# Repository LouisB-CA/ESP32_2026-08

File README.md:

# A Project for ESP32 Scratchwork
**2026-08-10**

### Rough Timeline
* Aug 2026 -- write sketches for breadboard circuit
* Sep 2026 -- layout and assemble perfboard version
* Oct 2026 -- write sketches for the perfboard assembly

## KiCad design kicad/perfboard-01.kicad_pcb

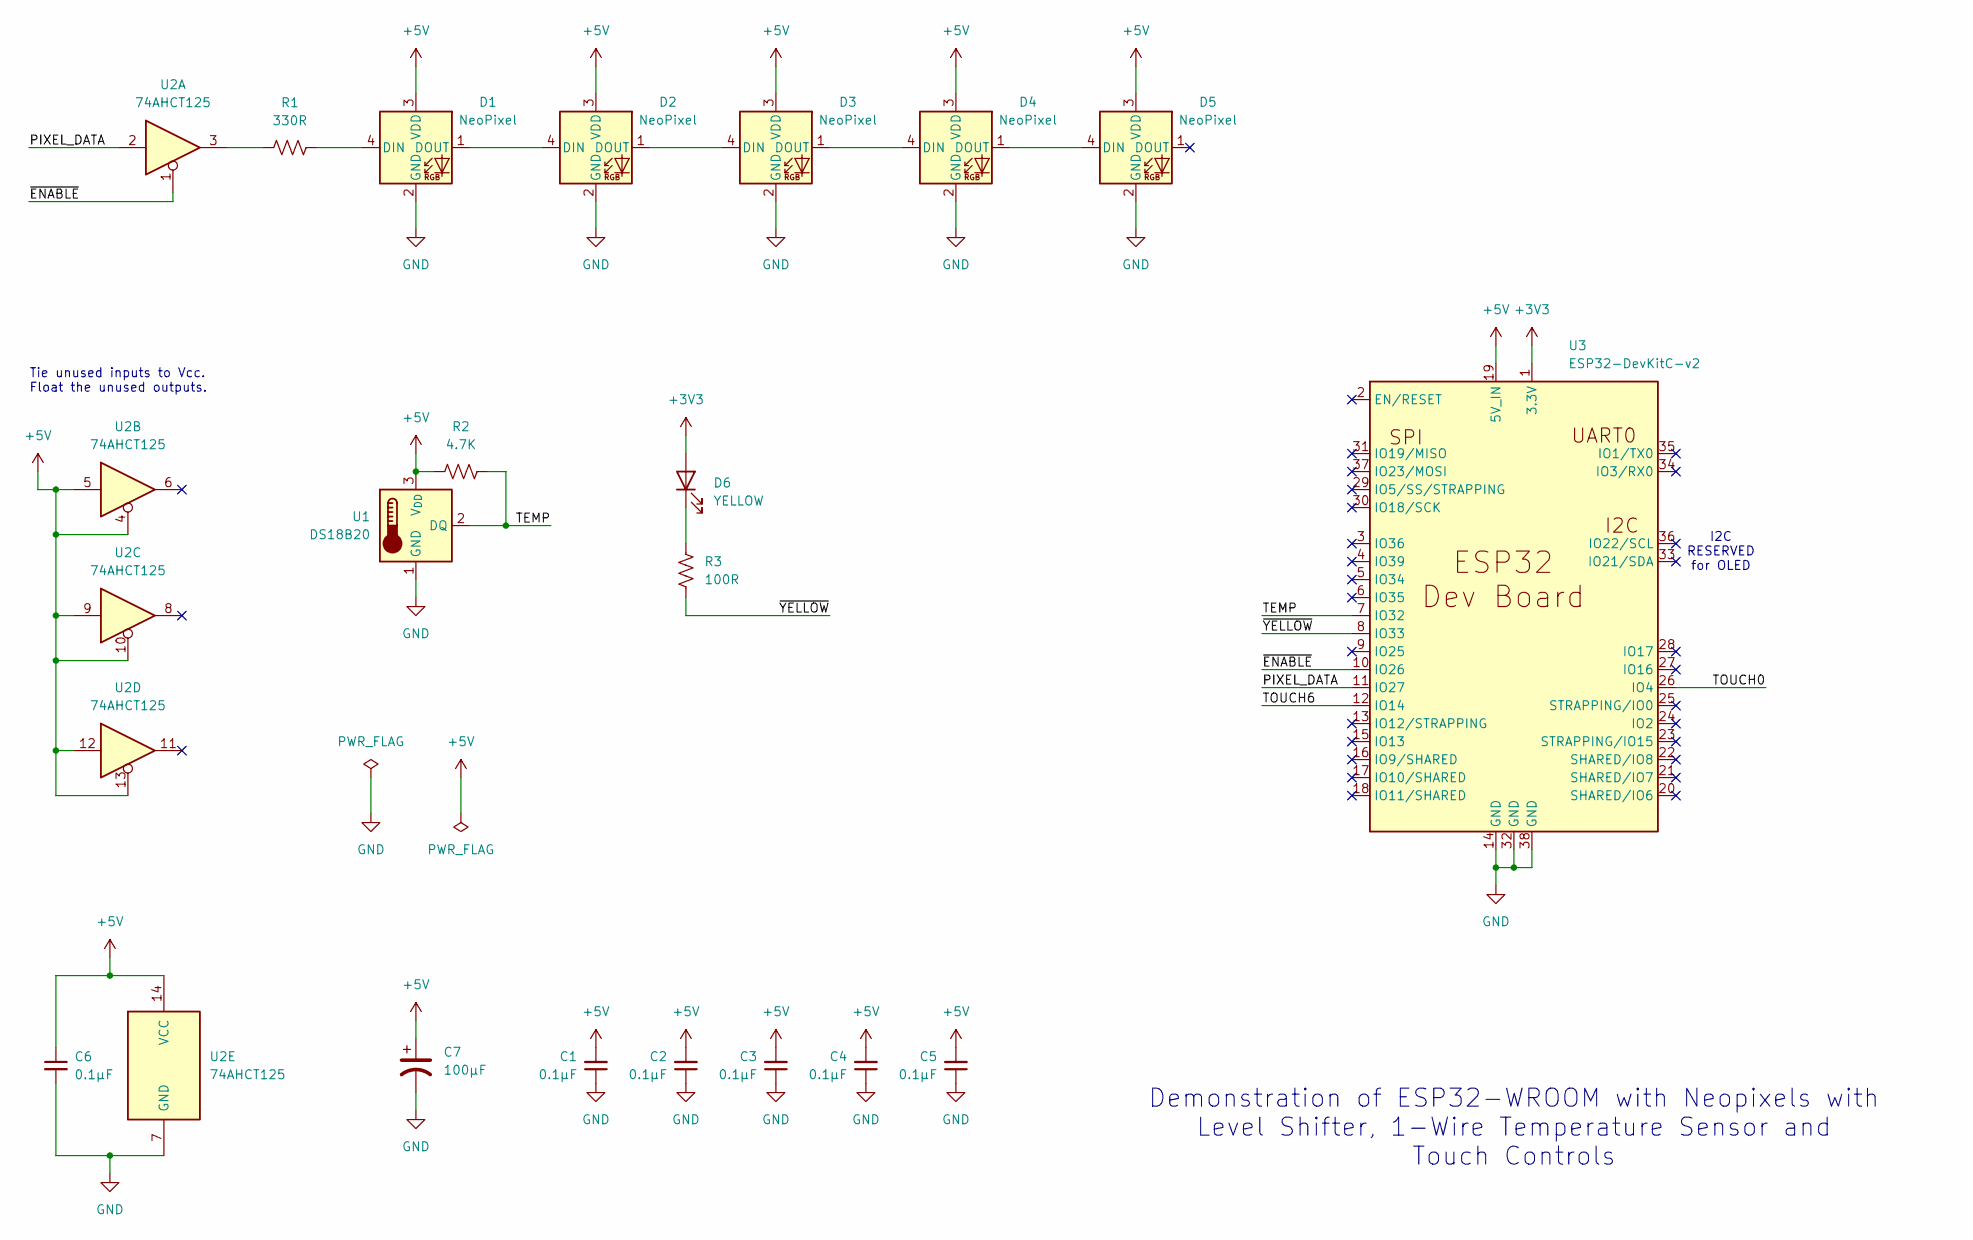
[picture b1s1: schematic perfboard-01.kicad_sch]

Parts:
C1, C2, C3, C4, C5, C6: 0.1µF; C_Disc_D3.4mm_W2.1mm_P2.50mm
C7: 100µF; C_Radial_D5.0mm_H11.0mm_P2.00mm
D1, D2, D3, D4, D5: NeoPixel; Neopixel_1x04_P2.54mm_Vertical_Mounted
D6: YELLOW; LED_D3.0mm_Horizontal_O6.35mm_Z6.0mm
R1: 330R; R_Axial_DIN0309_L9.0mm_D3.2mm_P12.70mm_Horizontal
R2: 4.7K; R_Axial_DIN0207_L6.3mm_D2.5mm_P10.16mm_Horizontal
R3: 100R; R_Axial_DIN0207_L6.3mm_D2.5mm_P10.16mm_Horizontal
U1: DS18B20; TO-92_Inline
U2: 74AHCT125; CERDIP-14_W7.62mm_SideBrazed
U3: ESP32-DevKitC-v2; ESP32-DevKitC_inverted

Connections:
+3V3: D6.2 (A), U3.1 (3.3V)
+5V: C1.2, C2.2, C3.2, C4.2, C5.2, C6.1, C7.1, D1.3 (VDD), D2.3 (VDD), D3.3 (VDD), D4.3 (VDD), D5.3 (VDD), R2.1, U1.3 (V_{DD}), U2.4, U2.5, U2.9, U2.10, U2.12, U2.13, U2.14 (VCC), U3.19 (5V_IN)
/PIXEL_DATA: U2.2, U3.11 (IO27)
/TEMP: R2.2, U1.2 (DQ), U3.7 (IO32)
/TOUCH0: U3.26 (IO4)
/TOUCH6: U3.12 (IO14)
/~ENABLE: U2.1, U3.10 (IO26)
/~YELLOW: R3.2, U3.8 (IO33)
GND: C1.1, C2.1, C3.1, C4.1, C5.1, C6.2, C7.2, D1.2 (GND), D2.2 (GND), D3.2 (GND), D4.2 (GND), D5.2 (GND), U1.1 (GND), U2.7 (GND), U3.14 (GND), U3.32 (GND), U3.38 (GND)
unnamed: D1.4 (DIN), R1.2
unnamed: D1.1 (DOUT), D2.4 (DIN)
unnamed: D2.1 (DOUT), D3.4 (DIN)
unnamed: D3.1 (DOUT), D4.4 (DIN)
unnamed: D4.1 (DOUT), D5.4 (DIN)
unnamed: D6.1 (K), R3.1
unnamed: R1.1, U2.3

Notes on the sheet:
I2C RESERVED for OLED
Demonstration of ESP32-WROOM with Neopixels with Level Shifter, 1-Wire Temperature Sensor and Touch Controls
Tie unused inputs to Vcc. Float the unused outputs.

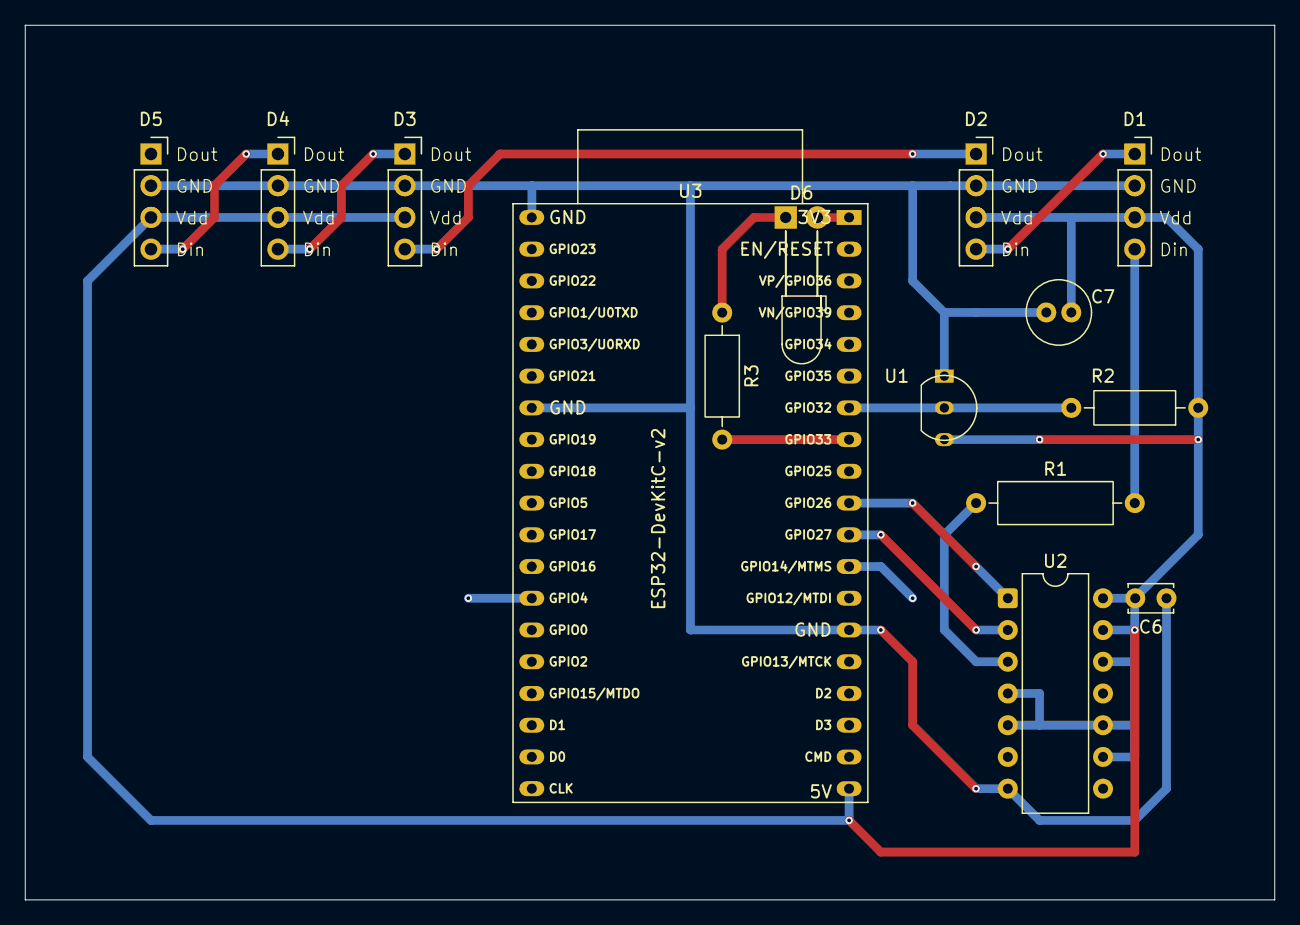
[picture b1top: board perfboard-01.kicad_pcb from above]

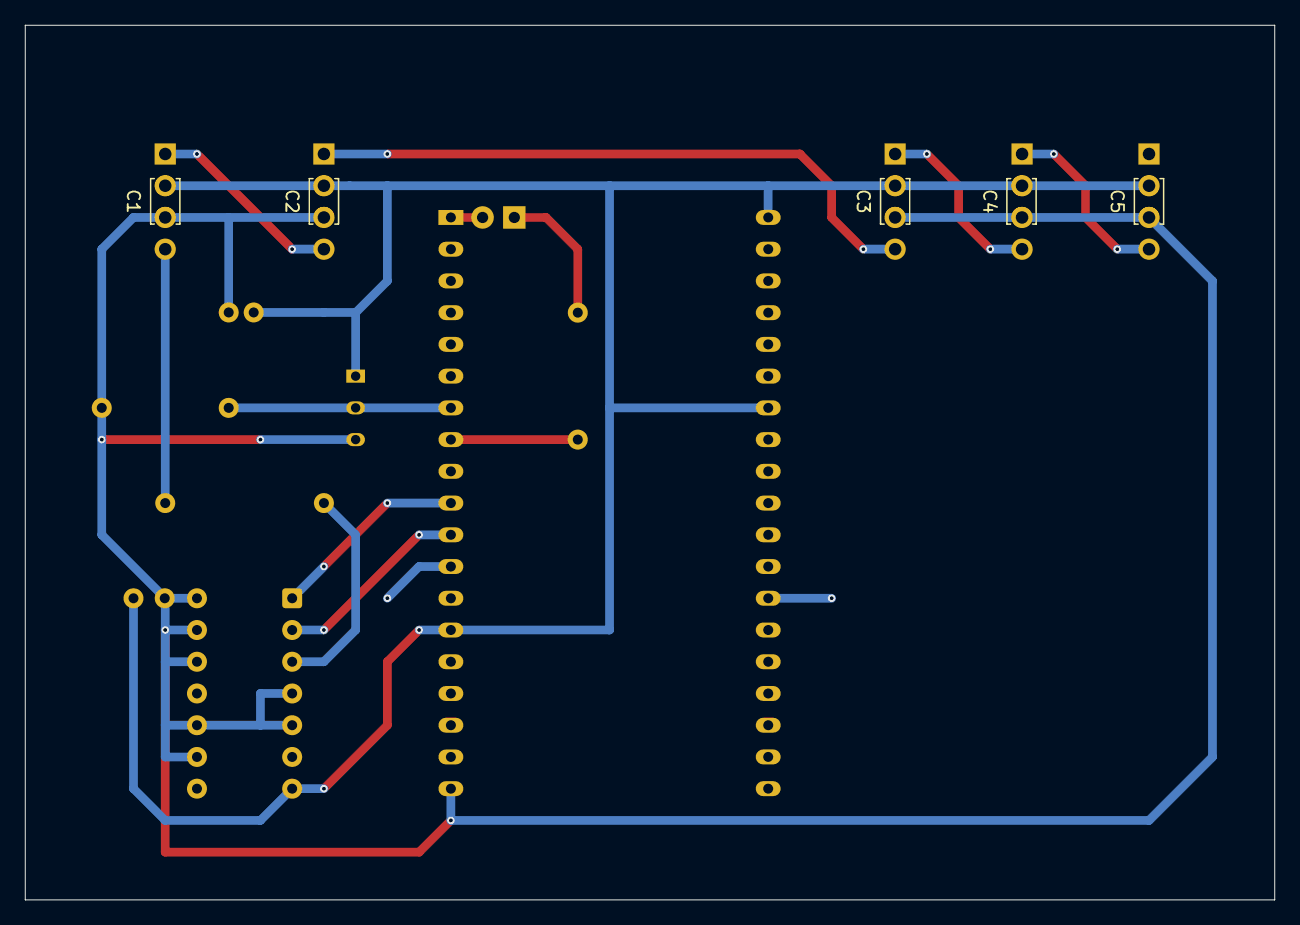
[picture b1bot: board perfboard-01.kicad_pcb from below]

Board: 2 copper layers, 100.0 x 70.0 mm, 19 parts (5 on the bottom side), 14 nets.
